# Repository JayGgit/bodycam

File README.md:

## bodycam

**Made for Hackclub's [Blueprint](blueprint.hackclub.com)**

A small bodycam that uploads footage to the cloud automatically. It was designed to be easily transported and attached onto a person. It saves the last 5 minutes of footage from before a recording starts.

## PCB and Schematic

## BOM
|Item Name                                   |Cost (before tax + shipping)|Link                                                                                                                                                                                                                                                                                                                                                                                                                                                                                                                                                                                                                                      |Quantity|Running Total (With tax & shipping)
|--------------------------------------------|----------------------------|------------------------------------------------------------------------------------------------------------------------------------------------------------------------------------------------------------------------------------------------------------------------------------------------------------------------------------------------------------------------------------------------------------------------------------------------------------------------------------------------------------------------------------------------------------------------------------------------------------------------------------------|--------|-----------------------------------
|Seeed Studio XIAO ESP32-S3 Sense            |$13.21                      |[Link](https://www.seeedstudio.com/XIAO-ESP32S3-Sense-p-5639.html)                                                                                                                                                                                                                                                                                                                                                                                                                                                                                                                                                                                |1       |$19.24                     
|PNY 32GB Elite Class 10 U1 microSDHC        |$8.40                       |[Link](https://www.amazon.com/PNY-Elite-microSDHC-Memory-P-SDU32GU185GW-GE/dp/B07R8GVGN9?th=1)                                                                                                                                                                                                                                                                                                                                                                                                                                                                                                                                                    |1       |                           
|Lithium-Ion Polymer Battery - 3.7v 2500mAh  |$9.99                       |[Link](https://www.amazon.com/605060-2500mAh-Lithium-Rechargeable-Connector/dp/B0C2KP2PP6/ref=sr_1_3?crid=1AECK9ZASP6BA&dib=eyJ2IjoiMSJ9.-jGVXbxw660XuEgFKsZsSNMgUhMcnQtebE8CJdjgw1nuahYbJN3PEz_FvpkNYIFZYheNXGey8GRxkCQ8voycHv4i_xOGOOvru8r64s8xwblZLz1IHG71Mdlvo4noXRtAcVRVBezHOo6xI_7RxtHEI9or7-3uuJjr2_WqzLDEBRvtUwpntCoi5D7uW4dgtiKvExPo8k_yn3RytmX_CNaT8gjW0sSWYgKNRF4AL7_agZmP8LQV5KCDoIJX36Oz9vOMgWWW293fxnnj36OriXCD_Jap-Yj8raZ3EDsFHAmdjyQ.ht3zuJ8NavIECDSOst57zXqBbtDFZZbdDguIEplycaM&dib_tag=se&keywords=PKCELL%20LP785060&qid=1767219117&sprefix=pkcell%20lp785060,aps,173&sr=8-3)                                                   |1       |$39.42                  
|JST-PH connector                            |$2.24                       |[Link](https://www.aliexpress.us/item/3256808498055527.html?spm=a2g0o.productlist.main.26.2e66ohfjohfjta&algo_pvid=ac01c2ef-2d65-4aab-a33f-4bb1e4202de7&algo_exp_id=ac01c2ef-2d65-4aab-a33f-4bb1e4202de7-25&pdp_ext_f=%7B%22order%22:%22312%22,%22eval%22:%221%22,%22fromPage%22:%22search%22%7D&pdp_npi=6@dis!USD!1.95!1.95!!!1.95!1.95!@21030a4b17672203417798126e27eb!12000046253280571!sea!US!6205085976!X!1!0!n_tag:-29919;d:a2c3a496;m03_new_user:-29895&curPageLogUid=16DoS7iR5H7R&utparam-url=scene:search%7Cquery_from:%7Cx_object_id:1005008684370279%7C_p_origin_prod:)|1       |                                  
|0.91 OLED screen                            |$1.91                       |[Link](https://www.aliexpress.us/item/3256807613276538.html?spm=a2g0o.productlist.main.15.12d83509cQtD9q&algo_pvid=39f26220-cdf9-4b2c-909f-514857fd7e02&algo_exp_id=39f26220-cdf9-4b2c-909f-514857fd7e02-14&pdp_ext_f=%7B%22order%22:%22469%22,%22eval%22:%221%22,%22fromPage%22:%22search%22%7D&pdp_npi=6@dis!USD!3.36!1.91!!!23.38!13.27!@2101ea8c17672179253546400ec2f6!12000042242093250!sea!US!6205085976!X!1!0!n_tag:-29919;d:a2c3a496;m03_new_user:-29895;pisId:5000000196731661&curPageLogUid=goql1yiWadS1&utparam-url=scene:search%7Cquery_from:%7Cx_object_id:1005007799591290%7C_p_origin_prod:)                                       |1       |                                  
|Tactile Tact Mini Push Button Switch (20pcs)|$2.53                       |[Link](https://www.aliexpress.us/item/3256805866888485.html?spm=a2g0o.productlist.main.11.6776p6Ctp6CtMf&algo_pvid=5aa1c84f-5190-49ee-bc2e-ea2515e87dab&algo_exp_id=5aa1c84f-5190-49ee-bc2e-ea2515e87dab-10&pdp_ext_f=%7B%22order%22:%2233%22,%22eval%22:%221%22,%22fromPage%22:%22search%22%7D&pdp_npi=6@dis!USD!2.24!2.24!!!15.58!15.58!@2101e81117672178832467336e69e4!12000035552828498!sea!US!6205085976!X!1!0!n_tag:-29919;d:a2c3a496;m03_new_user:-29895&curPageLogUid=UekDaiqG9y5N&utparam-url=scene:search%7Cquery_from:%7Cx_object_id:1005006053203237%7C_p_origin_prod:)                                                               |1       |$48.03                            
|PCB (5pcs)                                  |$0.00 (Will fund myself)     |[Link](https://jlcpcb.com)                                                                                                                                                                                                                                                                                                                                                                                                                                                                                                                                                                                                                        |1       |$48.03                            
|                                            |                            |                                                                                                                                                                                                                                                                                                                                                                                                                                                                                                                                                                                                                                          |        |$48.03                               
|                                            |                            |                                                                                                                                                                                                                                                                                                                                                                                                                                                                                                                                                                                                                                          |        |

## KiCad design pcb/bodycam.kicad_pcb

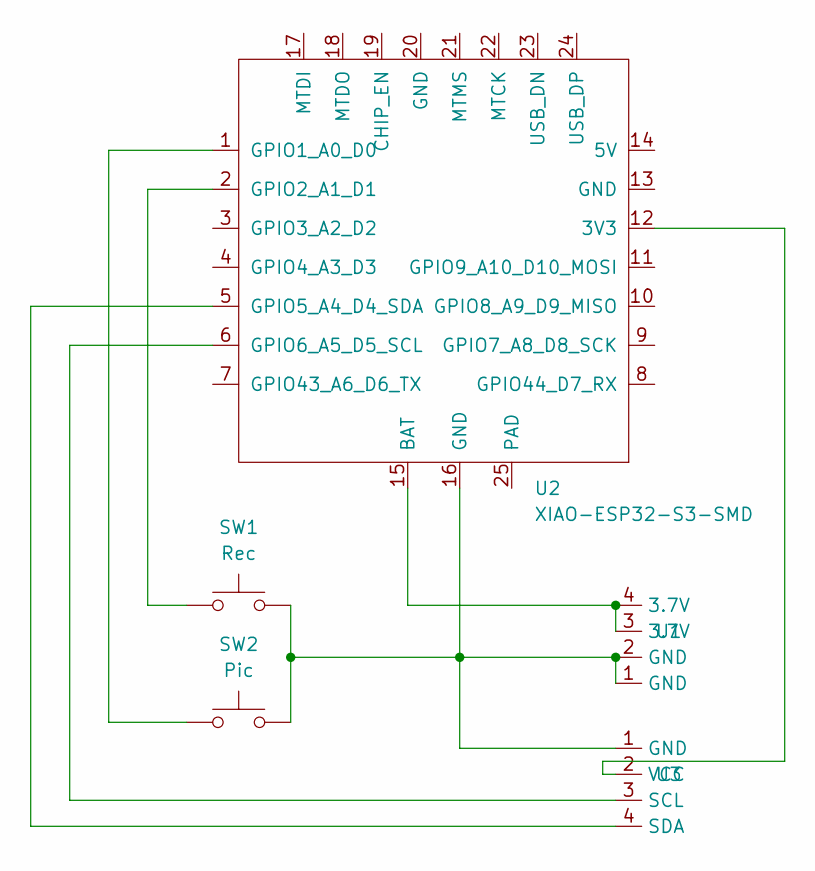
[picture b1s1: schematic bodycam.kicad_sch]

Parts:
SW1: Rec; SW_PUSH_6mm
SW2: Pic; SW_PUSH_6mm
U1: JST-PH 2-Pin SMT Right Angle Breakout Board
U2: XIAO-ESP32-S3-SMD; XIAO-ESP32S3-SMD
U3: SSD1306-0.91-OLED-4pin-128x32

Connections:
unnamed: U2.12 (3V3), U3.2 (VCC)
unnamed: U1.3 (3.7V), U1.4 (3.7V), U2.15 (BAT)
unnamed: SW2.1, U2.1 (GPIO1_A0_D0)
unnamed: SW1.1, U2.2 (GPIO2_A1_D1)
unnamed: U2.5 (GPIO5_A4_D4_SDA), U3.4 (SDA)
unnamed: U2.6 (GPIO6_A5_D5_SCL), U3.3 (SCL)
unnamed: SW1.2, SW2.2, U1.1 (GND), U1.2 (GND), U2.16 (GND), U3.1 (GND)

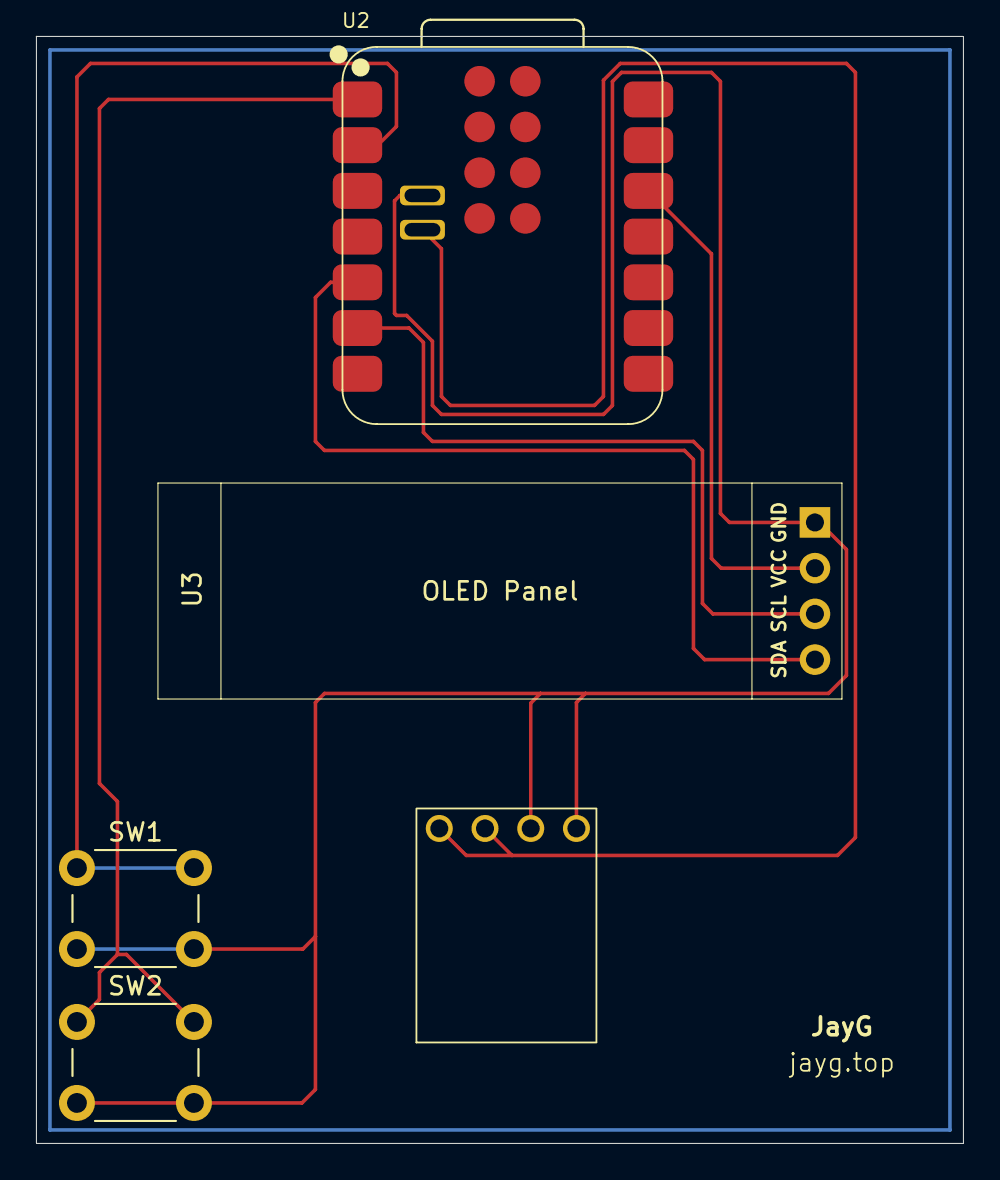
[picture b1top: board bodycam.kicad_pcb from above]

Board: 2 copper layers, 51.5 x 61.5 mm, 5 parts (0 on the bottom side), 7 nets.

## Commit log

2025-12-31 init
2025-12-31 Started circuitpython. It grabs the pins of the rec and pic button and finds when it is true. Also inits the camera.
2025-12-31 Finished very rough cloud service
2025-12-31 Firmware, PCB, and CAD
2025-12-31 Added image for the readme
2025-12-31 Enhance README with project details and BOM
    Added detailed project description, images, and BOM.
2025-12-31 Updated BOM
2025-12-31 Fixed BOM formatting
2025-12-31 Added full .step model
2026-02-15 Updated CAD to the updated case cover
2026-02-15 Actually fixed the cover
2026-02-15 Fixed lid tolerances
